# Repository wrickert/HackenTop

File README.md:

The goal here is to create a low cost laptop inspired in the was as Andrew 'Bunnie' Huang's Novena Laptop. It will be designed around the Raspberry Pi 3+ (CM3+) Compute Module. The idea is the allow easy upgrade as new compute modules are released. Monitor will be an external component to begin with.

22May - I returned to this project after nearly a year. The power requirements that looked daunting don't seem so bad now. <br>
26May - Completed first breakout board and ordered from JCLPCB<br>

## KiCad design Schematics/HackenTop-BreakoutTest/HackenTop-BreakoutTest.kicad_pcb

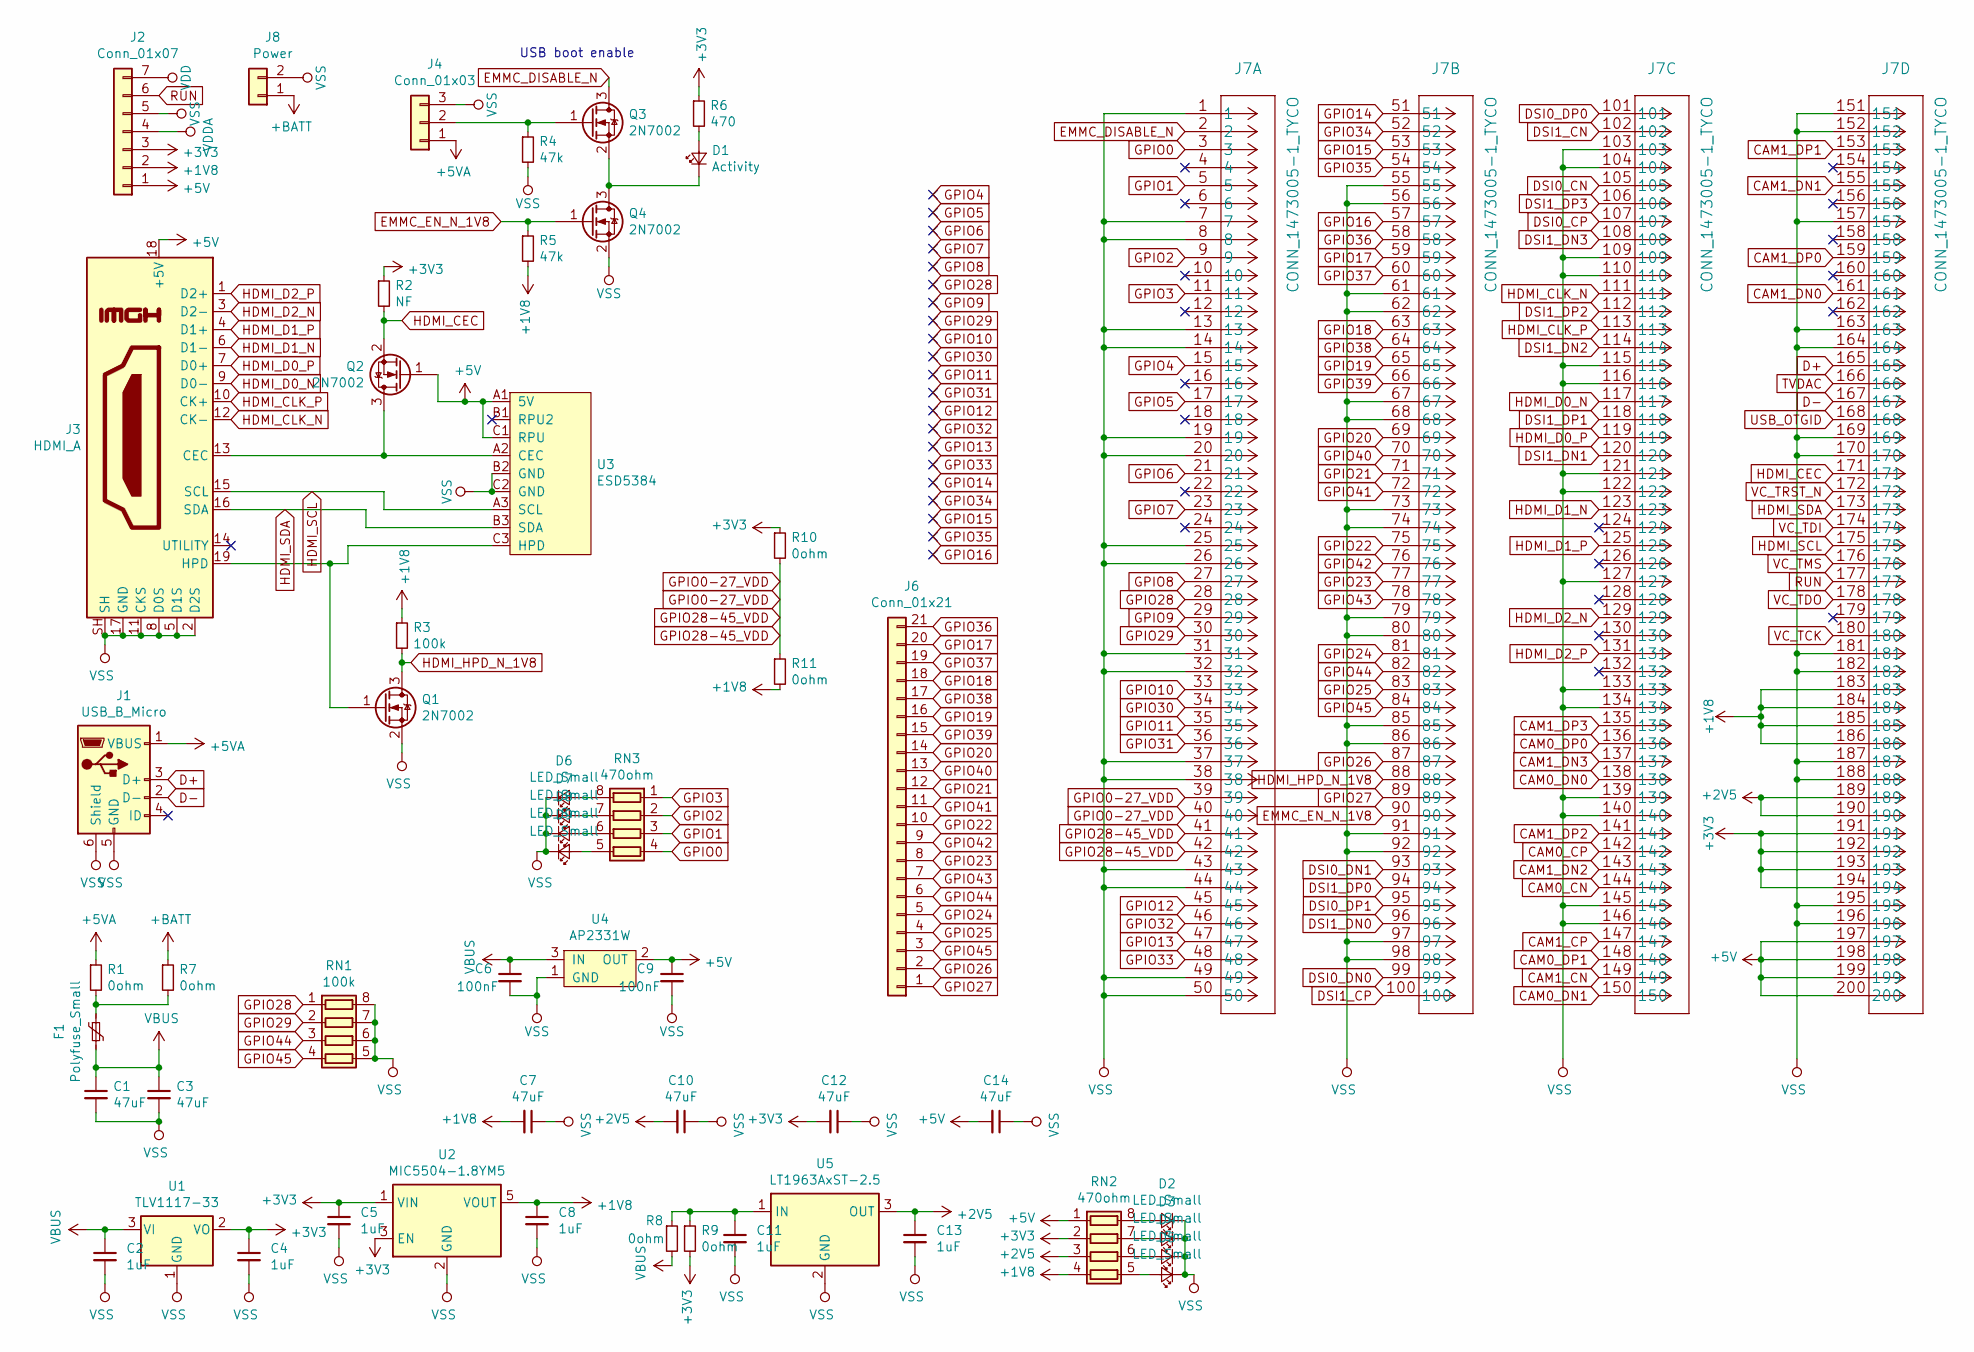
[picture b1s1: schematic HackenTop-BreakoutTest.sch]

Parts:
C1, C3, C7, C10, C12, C14: 47uF; C_0805_2012Metric
C2, C4, C5, C8, C11, C13: 1uF; C_0805_2012Metric
C6, C9: 100nF; C_0805_2012Metric
D1: Activity; LED_0603_1608Metric
D2, D3, D4, D5, D6, D7, D8, D9: LED_Small; LED_0603_1608Metric
F1: Polyfuse_Small; Fuse_1812_4532Metric
J1: USB_B_Micro; USB_Micro-B_Jing
J2: Conn_01x07; PinHeader_1x07_P2.54mm_Vertical
J3: HDMI_A; HDMI-jing
J4: Conn_01x03; PinHeader_1x03_P2.54mm_Vertical
J6: Conn_01x21; PinHeader_1x21_P2.54mm_Vertical
J7: CONN_1473005-1_TYCO; TE_1473149-4
J8: Power; TerminalBlock_RND_205-00012_1x02_P5.00mm_Horizontal
Q1, Q2, Q3, Q4: 2N7002; DMG1012T
R1, R7, R8, R9, R10, R11: 0ohm; R_0805_2012Metric
R2: NF; R_0805_2012Metric
R3: 100k; R_0805_2012Metric
R4, R5: 47k; R_0805_2012Metric
R6: 470; R_0805_2012Metric
RN1: 100k; R_Array_Convex_4x0603
RN2, RN3: 470ohm; R_Array_Convex_4x0603
U1: TLV1117-33; SOT-223-3_TabPin2
U2: MIC5504-1.8YM5; SOT-23-5
U3: ESD5384
U4: AP2331W; SOT-23
U5: LT1963AxST-2.5; SOT-23

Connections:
+1V8: C7.2, C8.1, J2.2, J7.183, J7.184, J7.185, J7.186, R3.1, R5.2, R11.2, RN2.4 (R4.1), U2.5 (VOUT)
+2V5: C10.2, C13.1, J7.189, J7.190, RN2.3 (R3.1), U5.3 (OUT)
+3V3: C4.1, C5.1, C12.2, J2.3, J7.191, J7.192, J7.193, J7.194, R2.1, R6.1, R9.2, R10.1, RN2.2 (R2.1), U1.2 (VO), U2.1 (VIN), U2.3 (EN)
+5V: C9.1, C14.2, J2.1, J3.18 (+5V), J7.197, J7.198, J7.199, J7.200, Q2.1 (G), RN2.1 (R1.1), U3.A1 (5V), U3.C1 (RPU), U4.2 (OUT)
+5VA: J1.1 (VBUS), J4.1, R1.1
+BATT: J8.1, R7.1
CAM0_CN: J7.144
CAM0_CP: J7.142
CAM0_DN0: J7.138
CAM0_DN1: J7.150
CAM0_DP0: J7.136
CAM0_DP1: J7.148
CAM1_CN: J7.149
CAM1_CP: J7.147
CAM1_DN0: J7.161
CAM1_DN1: J7.155
CAM1_DN2: J7.143
CAM1_DN3: J7.137
CAM1_DP0: J7.159
CAM1_DP1: J7.153
CAM1_DP2: J7.141
CAM1_DP3: J7.135
D+: J1.3 (D+), J7.165
D-: J1.2 (D-), J7.167
DSI0_CN: J7.105
DSI0_CP: J7.107
DSI0_DN0: J7.99
DSI0_DN1: J7.93
DSI0_DP0: J7.101
DSI0_DP1: J7.95
DSI1_CN: J7.102
DSI1_CP: J7.100
DSI1_DN0: J7.96
DSI1_DN1: J7.120
DSI1_DN2: J7.114
DSI1_DN3: J7.108
DSI1_DP0: J7.94
DSI1_DP1: J7.118
DSI1_DP2: J7.112
DSI1_DP3: J7.106
EMMC_DISABLE_N: J7.2, Q3.3 (D)
EMMC_EN_N_1V8: J7.90, Q4.1 (G), R5.1
GPIO0: J7.3, RN3.4 (R4.1)
GPIO0-27_VDD: J7.39, J7.40, J7.41, J7.42, R10.2, R11.1
GPIO1: J7.5, RN3.3 (R3.1)
GPIO2: J7.9, RN3.2 (R2.1)
GPIO3: J7.11, RN3.1 (R1.1)
GPIO4: J7.15
GPIO5: J7.17
GPIO6: J7.21
GPIO7: J7.23
GPIO8: J7.27
GPIO9: J7.29
GPIO10: J7.33
GPIO11: J7.35
GPIO12: J7.45
GPIO13: J7.47
GPIO14: J7.51
GPIO15: J7.53
GPIO16: J7.57
GPIO17: J6.20, J7.59
GPIO18: J6.18, J7.63
GPIO19: J6.16, J7.65
GPIO20: J6.14, J7.69
GPIO21: J6.12, J7.71
GPIO22: J6.10, J7.75
GPIO23: J6.8, J7.77
GPIO24: J6.5, J7.81
GPIO25: J6.4, J7.83
GPIO26: J6.2, J7.87
GPIO27: J6.1, J7.89
GPIO28: J7.28, RN1.1 (R1.1)
GPIO29: J7.30, RN1.2 (R2.1)
GPIO30: J7.34
GPIO31: J7.36
GPIO32: J7.46
GPIO33: J7.48
GPIO34: J7.52
GPIO35: J7.54
GPIO36: J6.21, J7.58
GPIO37: J6.19, J7.60
GPIO38: J6.17, J7.64
GPIO39: J6.15, J7.66
GPIO40: J6.13, J7.70
GPIO41: J6.11, J7.72
GPIO42: J6.9, J7.76
GPIO43: J6.7, J7.78
GPIO44: J6.6, J7.82, RN1.3 (R3.1)
GPIO45: J6.3, J7.84, RN1.4 (R4.1)
HDMI_CEC: J7.171, Q2.2 (S), R2.2
HDMI_CLK_N: J3.12 (CK-), J7.111
HDMI_CLK_P: J3.10 (CK+), J7.113
HDMI_D0_N: J3.9 (D0-), J7.117
HDMI_D0_P: J3.7 (D0+), J7.119
HDMI_D1_N: J3.6 (D1-), J7.123
HDMI_D1_P: J3.4 (D1+), J7.125
HDMI_D2_N: J3.3 (D2-), J7.129
HDMI_D2_P: J3.1 (D2+), J7.131
HDMI_HPD_N_1V8: J7.88, Q1.3 (D), R3.2
HDMI_SCL: J3.15 (SCL), J7.175, U3.A3 (SCL)
HDMI_SDA: J3.16 (SDA), J7.173, U3.B3 (SDA)
unnamed: C11.1, R8.1, R9.1, U5.1 (IN)
unnamed: D1.1 (K), Q3.2 (S), Q4.3 (D)
unnamed: D1.2 (A), R6.2
unnamed: D2.2 (A), RN2.8 (R1.2)
unnamed: D3.2 (A), RN2.7 (R2.2)
unnamed: D4.2 (A), RN2.6 (R3.2)
unnamed: D5.2 (A), RN2.5 (R4.2)
unnamed: D6.2 (A), RN3.8 (R1.2)
unnamed: D7.2 (A), RN3.7 (R2.2)
unnamed: D8.2 (A), RN3.6 (R3.2)
unnamed: D9.2 (A), RN3.5 (R4.2)
unnamed: F1.1, R1.2, R7.2
unnamed: J3.13 (CEC), Q2.3 (D), U3.A2 (CEC)
unnamed: J3.19 (HPD), Q1.1 (G), U3.C3 (HPD)
unnamed: J4.2, Q3.1 (G), R4.1
RUN: J2.6, J7.177
TVDAC: J7.166; also elsewhere on the board
USB_OTGID: J7.168
VBUS: C1.1, C2.1, C3.1, C6.1, F1.2, R8.2, U1.3 (VI), U4.3 (IN)
VC_TCK: J7.180
VC_TDI: J7.174
VC_TDO: J7.178
VC_TMS: J7.176
VC_TRST_N: J7.172
VDD: J2.7
VDDA: J2.4
VSS: C1.2, C2.2, C3.2, C4.2, C5.2, C6.2, C7.1, C8.2, C9.2, C10.1, C11.2, C12.1, C13.2, C14.1, D2.1 (K), D3.1 (K), D4.1 (K), D5.1 (K), D6.1 (K), D7.1 (K), D8.1 (K), D9.1 (K), J1.5 (GND), J1.6 (Shield), J2.5, J3.2 (D2S), J3.5 (D1S), J3.8 (D0S), J3.11 (CKS), J3.17 (GND), J3.20, J3.21, J3.22, J3.23, J3.SH, J4.3, J7.1, J7.7, J7.8, J7.13, J7.14, J7.19, J7.20, J7.25, J7.26, J7.31, J7.32, J7.37, J7.38, J7.43, J7.44, J7.49, J7.50, J7.55, J7.56, J7.61, J7.62, J7.67, J7.68, J7.73, J7.74, J7.79, J7.80, J7.85, J7.86, J7.91, J7.92, J7.97, J7.98, J7.103, J7.104, J7.109, J7.110, J7.115, J7.116, J7.121, J7.122, J7.127, J7.133, J7.134, J7.139, J7.140, J7.145, J7.146, J7.151, J7.152, J7.157, J7.163, J7.164, J7.169, J7.170, J7.181, J7.182, J7.187, J7.188, J7.195, J7.196, J7.SH1, J7.SH2, J8.2, Q1.2 (S), Q4.2 (S), R4.2, RN1.5 (R4.2), RN1.6 (R3.2), RN1.7 (R2.2), RN1.8 (R1.2), U1.1 (GND), U2.2 (GND), U3.B2 (GND), U3.C2 (GND), U4.1 (GND), U5.2 (GND); also elsewhere on the board

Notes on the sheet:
USB boot enable

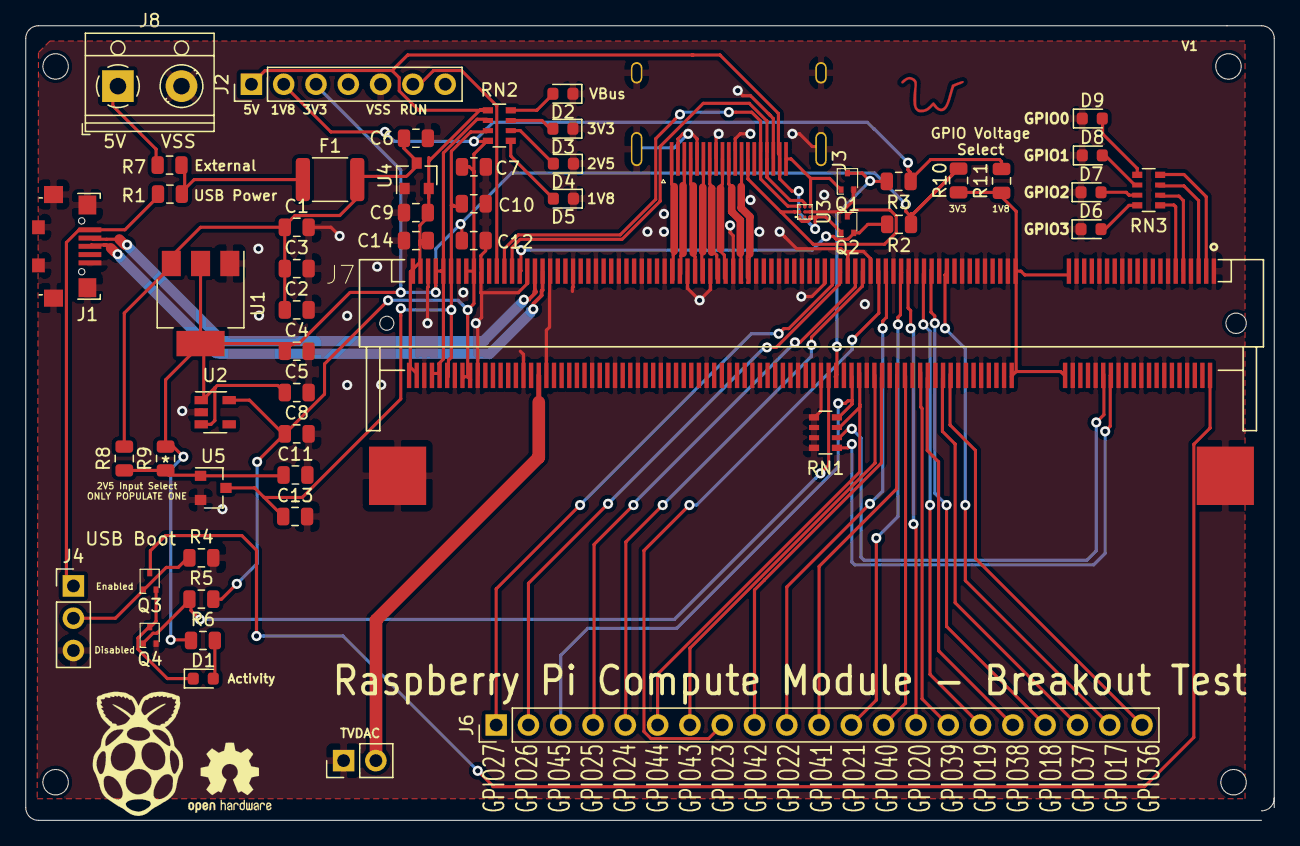
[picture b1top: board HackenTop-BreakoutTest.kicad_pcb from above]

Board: 2 copper layers, 98.2 x 62.5 mm, 57 parts (0 on the bottom side), 69 nets.

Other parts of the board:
Ref**: Val**; raspberry
Ref**#2: Val**; W
TVDAC: PinHeader_1x02_P2.54mm_Vertical

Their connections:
TVDAC: TVDAC.2; also elsewhere on the board
VSS: TVDAC.1; also elsewhere on the board

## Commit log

2019-05-25 Reorganized file structure and added to schematic
2019-05-26 Starting routing
2019-05-28 V1 ordered May26
